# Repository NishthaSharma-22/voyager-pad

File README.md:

# Voyagerpad

Voyagerpad is a 7 key macropad with an OLED Display.

## Features:
- 128x32 OLED Display
- 7 Keys

## PCB
The PCB was made in KiCad.

### Schematic

### PCB 
<div>

</div>

Silkscreen image credit: [Martin Melin – Voyager (via macpaint.org)](http://www.macpaint.org/images/1980s/martin_melin_voyager.gif)
## CAD Model:
The case was made in Autodesk Fusion.

### BOM

Here is everything needed to make this macropad:
- 1x XIAO RP2040
- 1x 0.91" 128x32 OLED Display
- 7x Cherry MX Switches
- 7x DSA Keycaps
- 1x Case

The gerbers, case STEP files and firmware are all in <code>/production</code> for anyone who wants to make voyagerpad! :)

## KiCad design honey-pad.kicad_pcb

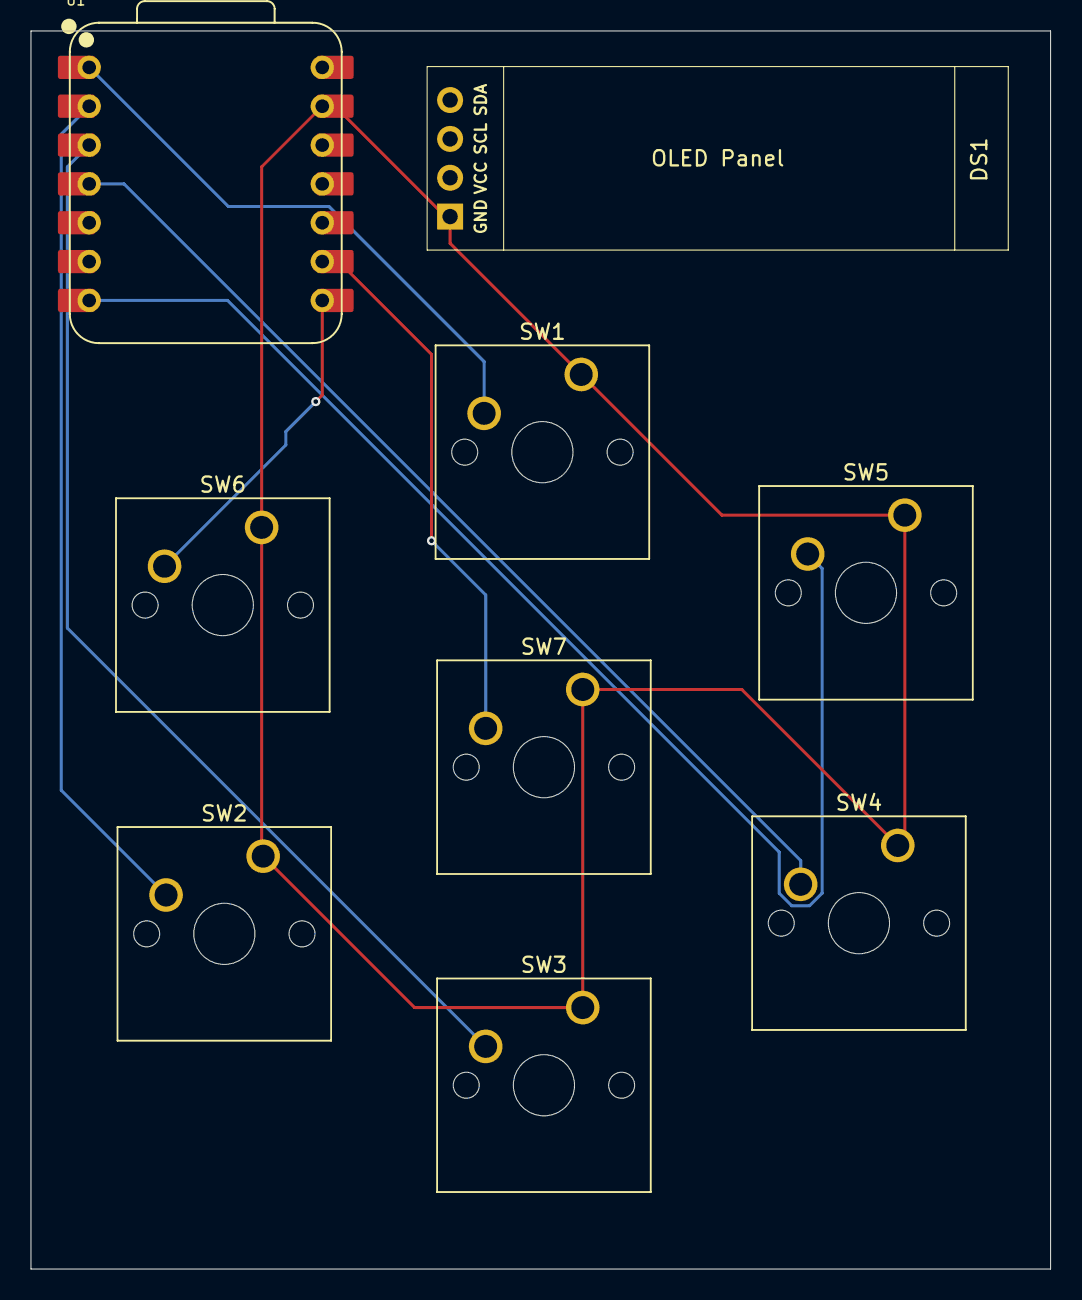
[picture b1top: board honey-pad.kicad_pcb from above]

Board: 2 copper layers, 66.7 x 81.0 mm, 9 parts (0 on the bottom side), 8 nets.

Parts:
DS1: OLED-128O064D; SSD1306-0.91-OLED-4pin-128x32
SW1, SW2, SW3, SW4, SW5, SW6, SW7: SW_Push; SW_Cherry_MX_1.00u_PCB
U1: XIAO-RP2040-DIP; XIAO-RP2040-DIP (2)

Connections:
GND: DS1.1 (GND), SW1.1, SW2.1, SW3.1, SW4.1, SW5.1, SW6.1, SW7.1, U1.13 (GND)
sw1: SW1.2, U1.1 (GPIO26/ADC0/A0)
sw2: SW2.2, U1.2 (GPIO27/ADC1/A1)
sw3: SW3.2, U1.3 (GPIO28/ADC2/A2)
sw4: SW4.2, U1.4 (GPIO29/ADC3/A3)
sw5: SW5.2, U1.7 (GPIO0/TX)
sw6: SW6.2, U1.8 (GPIO1/RX)
sw7: SW7.2, U1.9 (GPIO2/SCK)

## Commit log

2025-07-27 reorganized proj files
2025-07-27 reorganized proj structure
2025-07-31 added CAD files
2025-07-31 updated file structure
2025-07-31 updated pcb files
2025-07-31 added kmk firmware
2025-07-31 updated prod folder
2025-07-31 added proj images
2025-07-31 updated assets
2025-07-31 updated cad step files
2025-08-02 added bottom case
2025-08-02 added complete case image
2025-08-02 added case images
2025-08-02 deleted step files
2025-08-02 updated cad_model.png
2025-08-08 updated top case
2025-08-16 added top_case
2025-08-16 updated top case file for prod
2025-08-16 added the correct top_case
2025-08-16 updated cad file structure
